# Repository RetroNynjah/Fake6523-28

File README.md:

# Fake6523-28
This is a replacement for the 28-pin version of the MOS 6523 tri-port interface used in the Commodore 1551 paddle.

This replacement is pretty much a scaled down version of the 40-pin [Fake6523](https://github.com/go4retro/Fake6523) created by Jim Brain. 
The verilog code for the CPLD is based on code created by Maciej Witkowiak for the [TCBM2SD](https://github.com/ytmytm/plus4-tcbm2sd).  

## About the 6523

There is no datasheet available for the 28-pin version of the 6523. I'm guessing it was a modification that was made exclusively for the 1551 to fit in the paddle. They seem to be branded either 6523T or 6523A. 
It is quite similar to the 40-pin version but instead of three 8-bit ports it only has one 8-bit port (A) and two 2-bit ports (B and C). Some [old instructions](ref/1551-tia.gif) were available that let you replace a 28-pin 6523 with a 40-pin 6523 or 6525 using an adapter. I based my PCB design on those instructions.

I've tested a real 6523T to find out how it behaves in various conditions and this is what I found. Some of it is obvious and some of it is my best guesses.  
The two 2-bit ports and their corresponding DDR registers are all 8-bit registers internally. The other six bits in a 2-bit port (let's call them extra bits) are all there. They are just not connected to any external pins.
Eight bits can be written to them and wile the bits are configured as outputs (1) in the DDR registers, the same eight bits can be read back from the port register.  
When the extra bits are switched to inputs (0) in the DDR register, they start to float. At first, they retain the data that was last written to the port register but after a second or so, the extra bits start to toggle. The behaviour may seem conistent but it only is until it isn't :)

## Design history

### Rev 1

Revision 1 is based on the obsolete, yet still available CPLD XC9572XL-10VQ64 (VQFP-64).  
I chose to replicate the output funtionality with eight bits in all ports in this version of the HDL. The extra bits are normally not used by the 1551 and the drive works fine without that functionality but if some third party software like a highly optimized loader would use the extra bits for anything, it feels good to have them there for compatibility.

The firmware for Rev 1 is available in the [rev1/hdl](rev1/hdl) folder. There are compiled files in jed and svf formats and the source code is available as a Xilinx ISE project.

### Rev 2
This was a development revision that wasn't released.

### Rev 3
Revision 3 was based on the still active CPLD ATF1504AS (TQFP-44) and PORTB and PORTC was limited internally to two bits each due to space constraints and the unconnected extra bits in PORTB and PORTC always returned 0's. This normally doesn't affect the functionality of the drive and would only be a problem if someone would use these unconnected registers for something. I'm not aware of any software that does that.  
The ATF1504AS is a 5V part. No voltage regulator is necessary and the Atmel CPLD is cheaper than the Xilinx CPLD so the design is simpler and cheaper than the Xilinx design.  
The firmware for Rev 3 is available in the [rev3/hdl](rev3/hdl) folder. There are compiled files in jed and svf formats and the source code is available as a ProChip designer project.  
The rev 3 firmware is only compatible with rev 3 boards.

### Rev 4

Revision 4 is based on the same ATF1504AS CPLD as rev 3. The difference compared to rev 3 is that it once again enables all eight bits in all three port registers. This required a new PCB layout.  
The firmware for Rev 4 is available in the [rev4/hdl](rev4/hdl) folder. There are compiled files in jed and svf formats and the source code is available as a ProChip designer project.  
The rev 4 firmware is only compatible with rev 4 boards.

## Compatibility
The Fake6523-28 has not gone through any long term testing so **use at your own risk**.  
It has briefly been tested as a 1551 paddle TPI together with:
* 1551 CPU
    * MOS 6510T
    * Monotech 6502
* 1551 TPI
    * MOS 6525A
    * Fake6523
* Plus/4 CPUs and CPU replacements
    * MOS 8501R1
    * Zaxon FGPA
    * 6510 adapter
    * dmantione (6502)
    * Monotech (6502)
    * Firecpu7501 (6502)
* Plus/4 Kernal
    * CBM original
    * 6510 Kernal hack
    * JiffyDOS
* Plus/4 PLA
    * MOS 251641-02
    * PLA16V8
    * Retroninja CPLD PLA
* Paddle PLA
    * Original 251641-03
    * FlashPLA 55/70ns
    * Retroninja CPLD PLA
    * Retroninja 16V8 PLA

Rev 3 has been tested even less but should hopefully work the same.

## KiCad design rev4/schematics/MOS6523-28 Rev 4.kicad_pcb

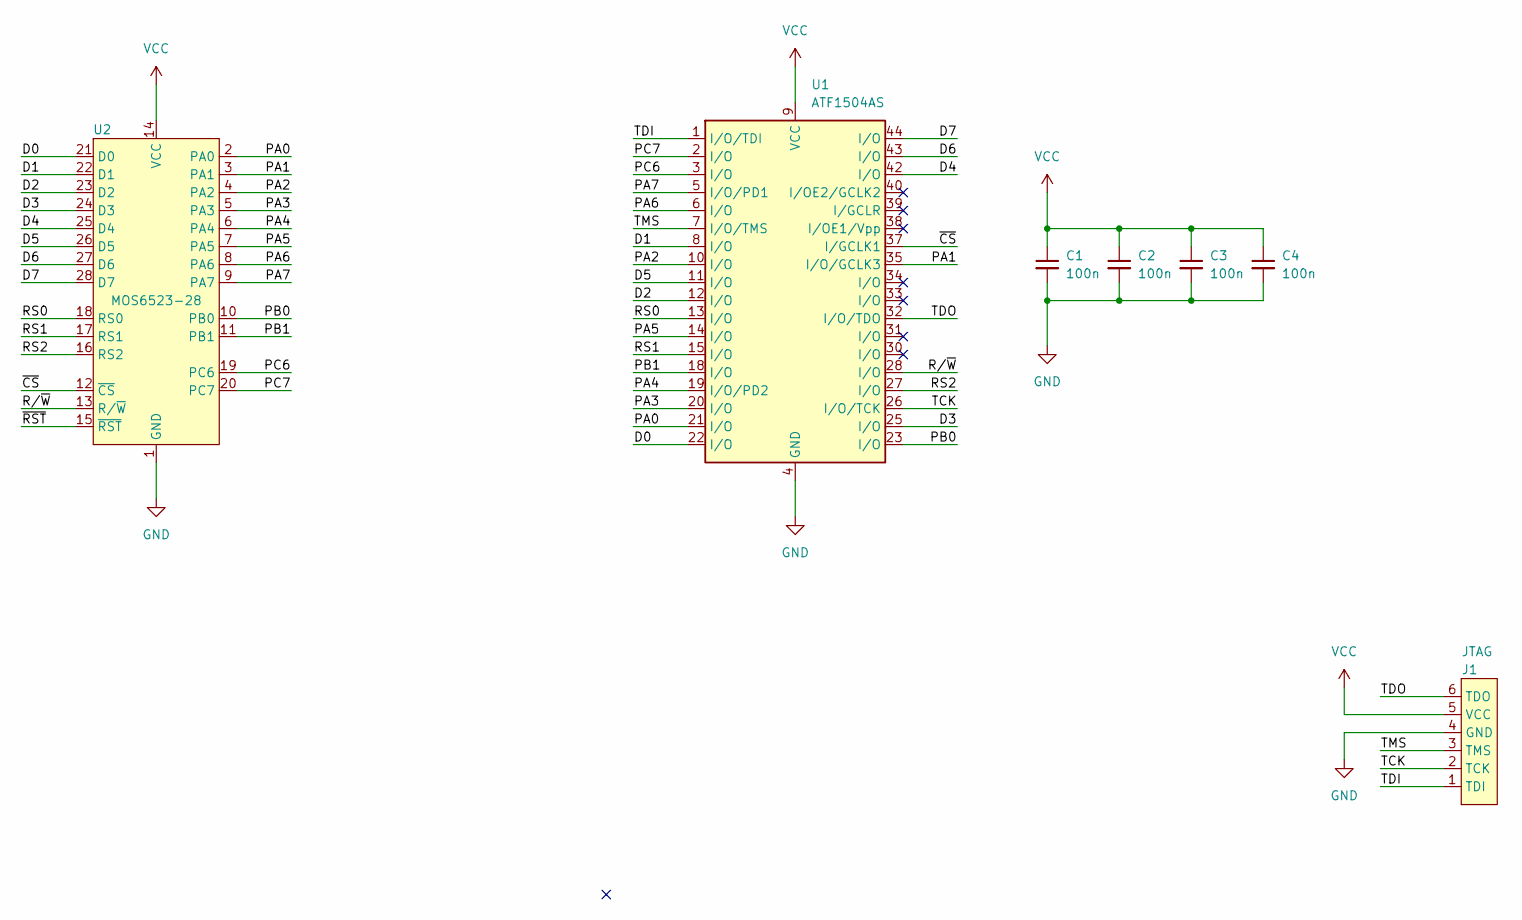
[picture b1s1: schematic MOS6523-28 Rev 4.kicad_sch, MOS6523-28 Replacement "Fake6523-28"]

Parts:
C1, C2, C3, C4: 100n; C_0603_1608Metric_Pad1.08x0.95mm_HandSolder
J1: JTAG; PinHeader_2x03_P2.54mm_Vertical
U1: ATF1504AS; TQFP-44_10x10mm_P0.8mm
U2: MOS6523-28; DIP-28_W15.24mm_BottomHeadersFlat

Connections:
/D0: U1.22 (I/O), U2.21 (D0)
/D1: U1.8 (I/O), U2.22 (D1)
/D2: U1.12 (I/O), U2.23 (D2)
/D3: U1.25 (I/O), U2.24 (D3)
/D4: U1.42 (I/O), U2.25 (D4)
/D5: U1.11 (I/O), U2.26 (D5)
/D6: U1.43 (I/O), U2.27 (D6)
/D7: U1.44 (I/O), U2.28 (D7)
/PA0: U1.21 (I/O), U2.2 (PA0)
/PA1: U1.35 (I/O/GCLK3), U2.3 (PA1)
/PA2: U1.10 (I/O), U2.4 (PA2)
/PA3: U1.20 (I/O), U2.5 (PA3)
/PA4: U1.19 (I/O/PD2), U2.6 (PA4)
/PA5: U1.14 (I/O), U2.7 (PA5)
/PA6: U1.6 (I/O), U2.8 (PA6)
/PA7: U1.5 (I/O/PD1), U2.9 (PA7)
/PB0: U1.23 (I/O), U2.10 (PB0)
/PB1: U1.18 (I/O), U2.11 (PB1)
/PC6: U1.3 (I/O), U2.19 (PC6)
/PC7: U1.2 (I/O), U2.20 (PC7)
/RS0: U1.13 (I/O), U2.18 (RS0)
/RS1: U1.15 (I/O), U2.17 (RS1)
/RS2: U1.27 (I/O), U2.16 (RS2)
/R/~W: U1.28 (I/O), U2.13 (R/~W)
/TCK: J1.2 (TCK), U1.26 (I/O/TCK)
/TDI: J1.1 (TDI), U1.1 (I/O/TDI)
/TDO: J1.6 (TDO), U1.32 (I/O/TDO)
/TMS: J1.3 (TMS), U1.7 (I/O/TMS)
/~CS: U1.37 (I/GCLK1), U2.12 (~CS)
/~RST: U2.15 (~RST)
GND: C1.2, C2.2, C3.2, C4.2, J1.4 (GND), U1.4 (GND), U1.16 (GND), U1.24 (GND), U1.36 (GND), U2.1 (GND)
VCC: C1.1, C2.1, C3.1, C4.1, J1.5 (VCC), U1.9 (VCC), U1.17 (VCC), U1.29 (VCC), U1.41 (VCC), U2.14 (VCC)

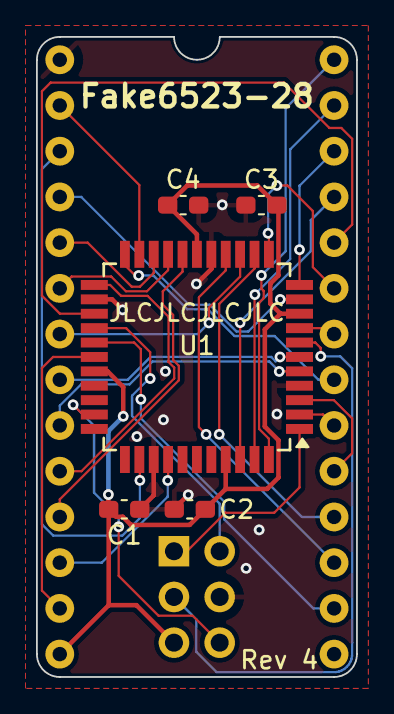
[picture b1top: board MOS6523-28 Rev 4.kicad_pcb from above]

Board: 2 copper layers, 17.8 x 35.6 mm, 7 parts (0 on the bottom side), 31 nets.

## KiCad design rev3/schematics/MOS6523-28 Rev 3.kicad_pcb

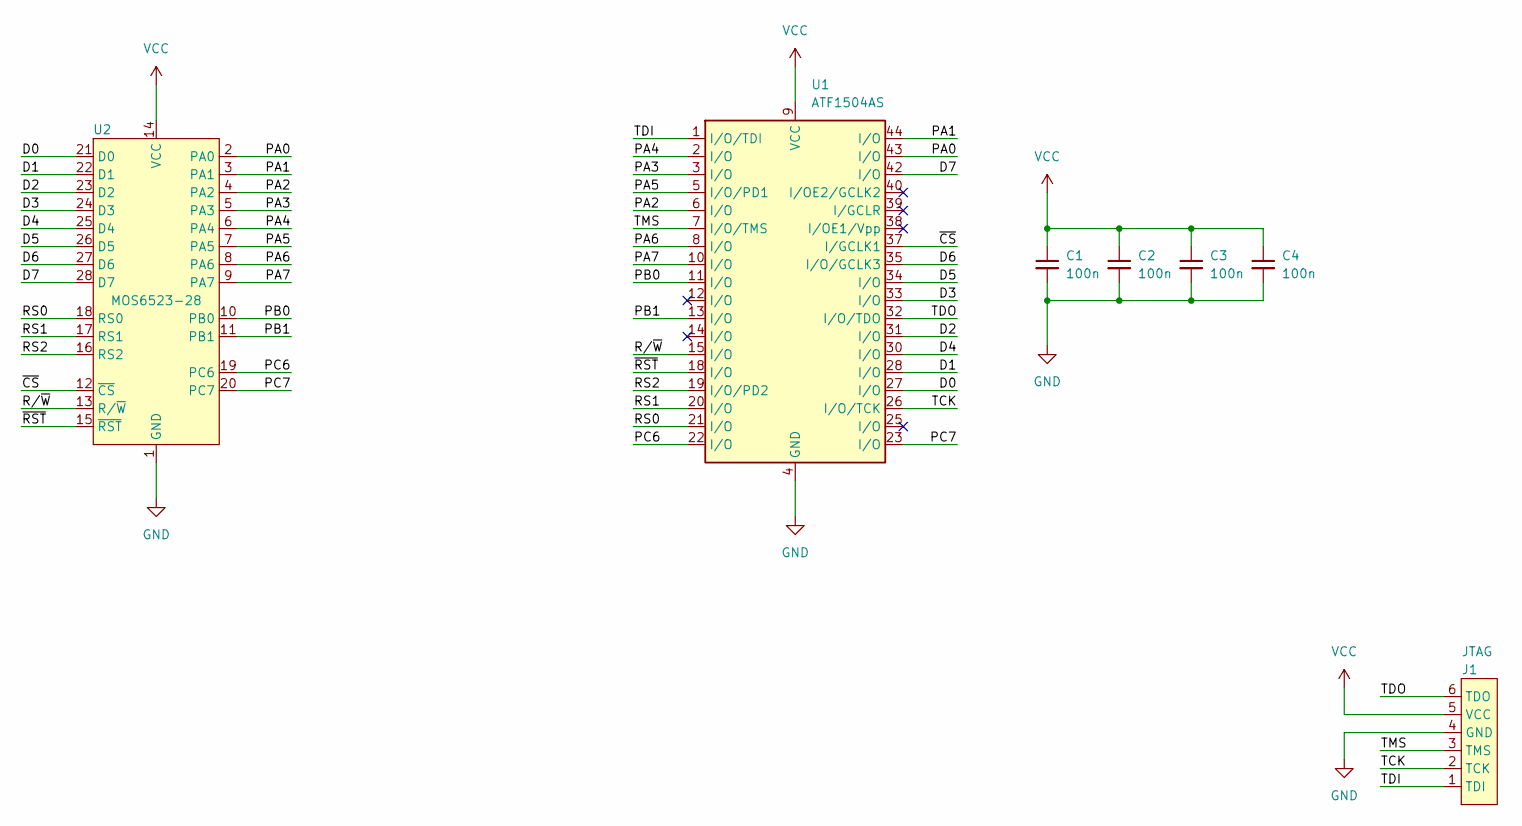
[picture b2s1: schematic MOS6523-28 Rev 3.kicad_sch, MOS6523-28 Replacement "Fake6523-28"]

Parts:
C1, C2, C3, C4: 100n; C_0603_1608Metric_Pad1.08x0.95mm_HandSolder
J1: JTAG; PinHeader_2x03_P2.54mm_Vertical
U1: ATF1504AS; TQFP-44_10x10mm_P0.8mm
U2: MOS6523-28; DIP-28_W15.24mm_BottomHeadersFlat

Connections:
/D0: U1.27 (I/O), U2.21 (D0)
/D1: U1.28 (I/O), U2.22 (D1)
/D2: U1.31 (I/O), U2.23 (D2)
/D3: U1.33 (I/O), U2.24 (D3)
/D4: U1.30 (I/O), U2.25 (D4)
/D5: U1.34 (I/O), U2.26 (D5)
/D6: U1.35 (I/O/GCLK3), U2.27 (D6)
/D7: U1.42 (I/O), U2.28 (D7)
/PA0: U1.43 (I/O), U2.2 (PA0)
/PA1: U1.44 (I/O), U2.3 (PA1)
/PA2: U1.6 (I/O), U2.4 (PA2)
/PA3: U1.3 (I/O), U2.5 (PA3)
/PA4: U1.2 (I/O), U2.6 (PA4)
/PA5: U1.5 (I/O/PD1), U2.7 (PA5)
/PA6: U1.8 (I/O), U2.8 (PA6)
/PA7: U1.10 (I/O), U2.9 (PA7)
/PB0: U1.11 (I/O), U2.10 (PB0)
/PB1: U1.13 (I/O), U2.11 (PB1)
/PC6: U1.22 (I/O), U2.19 (PC6)
/PC7: U1.23 (I/O), U2.20 (PC7)
/RS0: U1.21 (I/O), U2.18 (RS0)
/RS1: U1.20 (I/O), U2.17 (RS1)
/RS2: U1.19 (I/O/PD2), U2.16 (RS2)
/R/~W: U1.15 (I/O), U2.13 (R/~W)
/TCK: J1.2 (TCK), U1.26 (I/O/TCK)
/TDI: J1.1 (TDI), U1.1 (I/O/TDI)
/TDO: J1.6 (TDO), U1.32 (I/O/TDO)
/TMS: J1.3 (TMS), U1.7 (I/O/TMS)
/~CS: U1.37 (I/GCLK1), U2.12 (~CS)
/~RST: U1.18 (I/O), U2.15 (~RST)
GND: C1.2, C2.2, C3.2, C4.2, J1.4 (GND), U1.4 (GND), U1.16 (GND), U1.24 (GND), U1.36 (GND), U2.1 (GND)
VCC: C1.1, C2.1, C3.1, C4.1, J1.5 (VCC), U1.9 (VCC), U1.17 (VCC), U1.29 (VCC), U1.41 (VCC), U2.14 (VCC)

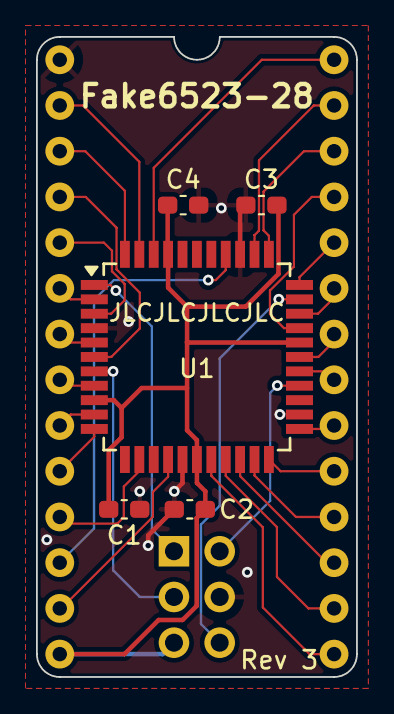
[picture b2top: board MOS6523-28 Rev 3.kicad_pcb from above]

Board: 2 copper layers, 17.8 x 35.6 mm, 7 parts (0 on the bottom side), 32 nets.

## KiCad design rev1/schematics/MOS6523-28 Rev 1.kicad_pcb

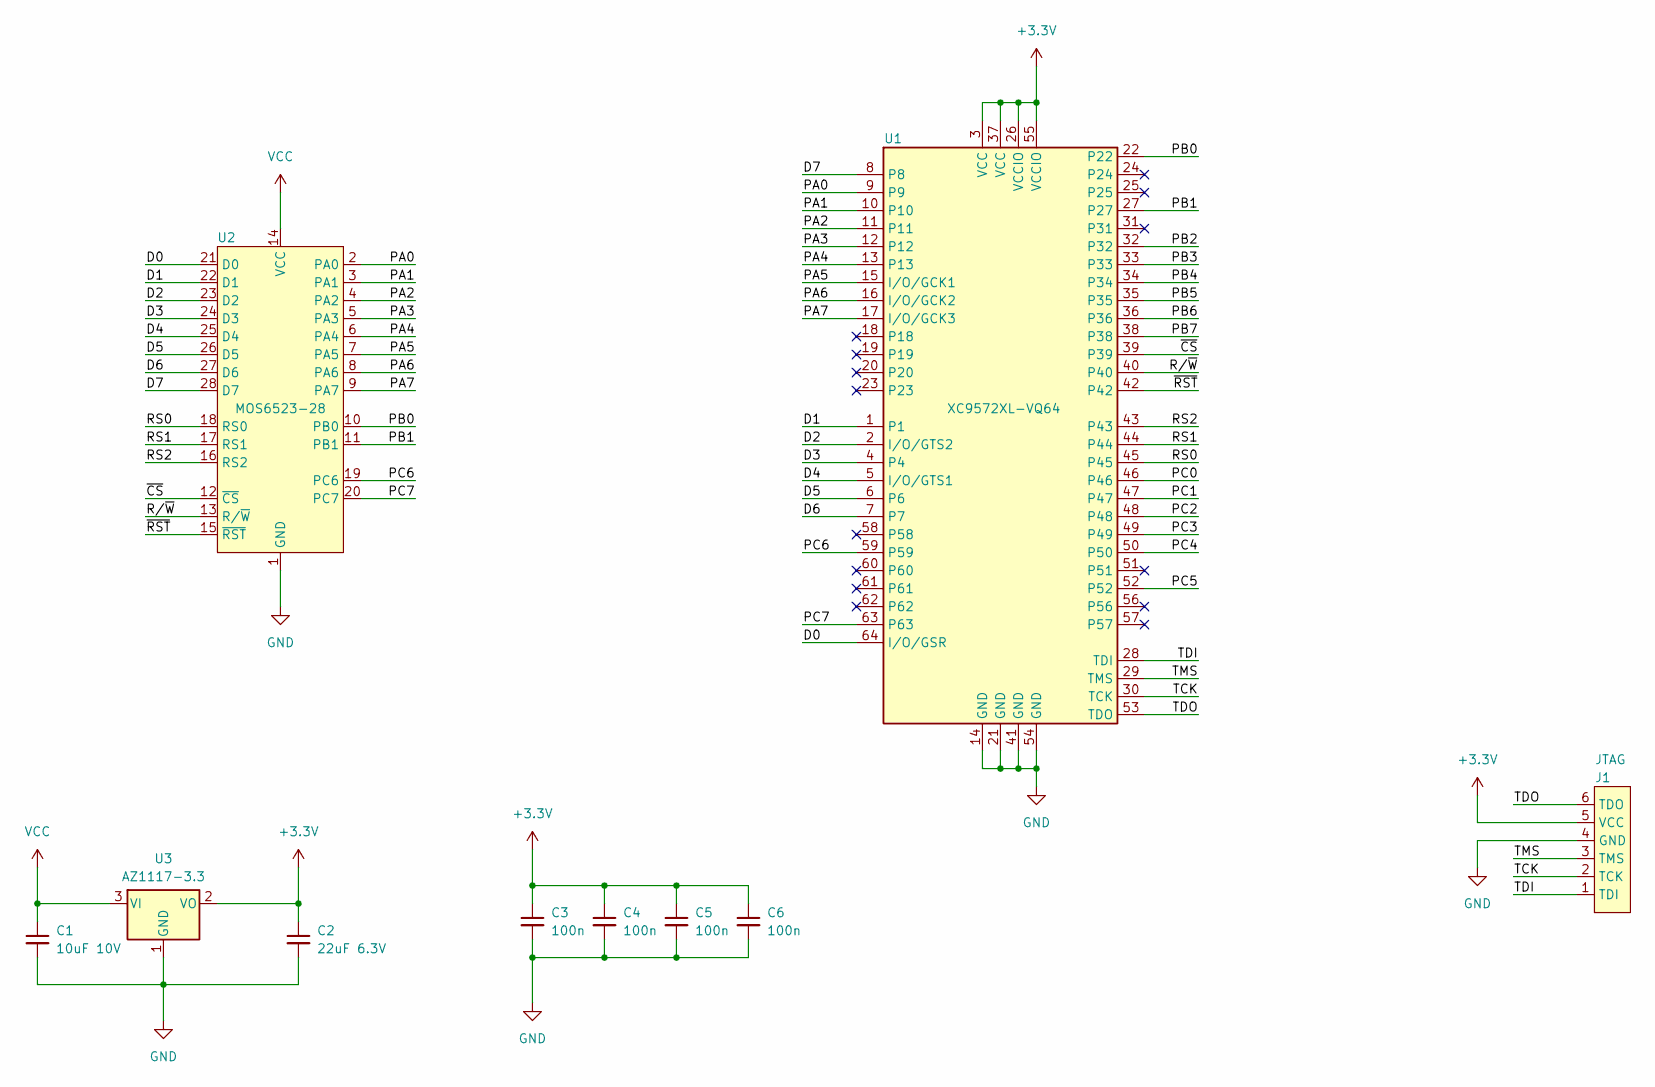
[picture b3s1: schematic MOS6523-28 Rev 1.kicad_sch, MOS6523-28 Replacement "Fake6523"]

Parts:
C1: 10uF 10V; C_0603_1608Metric_Pad1.08x0.95mm_HandSolder
C2: 22uF 6.3V; C_0603_1608Metric_Pad1.08x0.95mm_HandSolder
C3, C4, C5, C6: 100n; C_0603_1608Metric_Pad1.08x0.95mm_HandSolder
J1: JTAG; PinHeader_2x03_P2.54mm_Vertical
U1: XC9572XL-VQ64; TQFP-64_10x10mm_P0.5mm
U2: MOS6523-28; DIP-28_W15.24mm_BottomHeadersFlat
U3: AZ1117-3.3; SOT-89-3_Handsoldering

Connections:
+3.3V: C2.1, C3.1, C4.1, C5.1, C6.1, J1.5 (VCC), U1.3 (VCC), U1.26 (VCCIO), U1.37 (VCC), U1.55 (VCCIO), U3.2 (VO)
/D0: U1.64 (I/O/GSR), U2.21 (D0)
/D1: U1.1, U2.22 (D1)
/D2: U1.2 (I/O/GTS2), U2.23 (D2)
/D3: U1.4, U2.24 (D3)
/D4: U1.5 (I/O/GTS1), U2.25 (D4)
/D5: U1.6, U2.26 (D5)
/D6: U1.7, U2.27 (D6)
/D7: U1.8, U2.28 (D7)
/PA0: U1.9, U2.2 (PA0)
/PA1: U1.10, U2.3 (PA1)
/PA2: U1.11, U2.4 (PA2)
/PA3: U1.12, U2.5 (PA3)
/PA4: U1.13, U2.6 (PA4)
/PA5: U1.15 (I/O/GCK1), U2.7 (PA5)
/PA6: U1.16 (I/O/GCK2), U2.8 (PA6)
/PA7: U1.17 (I/O/GCK3), U2.9 (PA7)
/PB0: U1.22, U2.10 (PB0)
/PB1: U1.27, U2.11 (PB1)
/PB2: U1.32
/PB3: U1.33
/PB4: U1.34
/PB5: U1.35
/PB6: U1.36
/PB7: U1.38
/PC0: U1.46
/PC1: U1.47
/PC2: U1.48
/PC3: U1.49
/PC4: U1.50
/PC5: U1.52
/PC6: U1.59, U2.19 (PC6)
/PC7: U1.63, U2.20 (PC7)
/RS0: U1.45, U2.18 (RS0)
/RS1: U1.44, U2.17 (RS1)
/RS2: U1.43, U2.16 (RS2)
/R/~W: U1.40, U2.13 (R/~W)
/TCK: J1.2 (TCK), U1.30 (TCK)
/TDI: J1.1 (TDI), U1.28 (TDI)
/TDO: J1.6 (TDO), U1.53 (TDO)
/TMS: J1.3 (TMS), U1.29 (TMS)
/~CS: U1.39, U2.12 (~CS)
/~RST: U1.42, U2.15 (~RST)
GND: C1.2, C2.2, C3.2, C4.2, C5.2, C6.2, J1.4 (GND), U1.14 (GND), U1.21 (GND), U1.41 (GND), U1.54 (GND), U2.1 (GND), U3.1 (GND)
VCC: C1.1, U2.14 (VCC), U3.3 (VI)

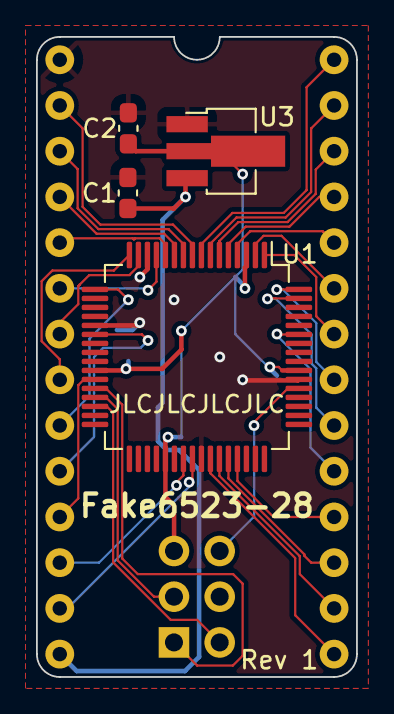
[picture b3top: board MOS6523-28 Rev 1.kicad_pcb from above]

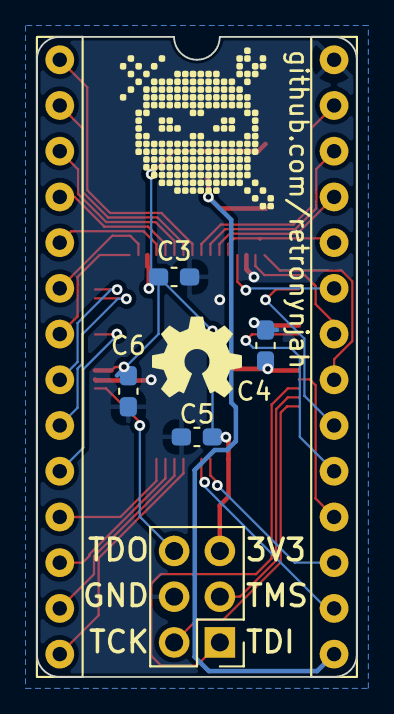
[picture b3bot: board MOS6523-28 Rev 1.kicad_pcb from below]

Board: 2 copper layers, 17.8 x 35.6 mm, 10 parts (5 on the bottom side), 33 nets.

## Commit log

2024-10-27 First upload
2024-10-31 Updated readme with pinout adn tested configurations
2024-11-03 HDL and README updated
    New HDL version with 8-bit registers for PRA & PRB. They read the internal databits if they are set as outputs.
    README updated after research
2025-01-27 Rev 3 released
    Released PCB rev 3 based on ATF1504
2025-01-27 Images corrected
2025-02-23 Update README.md
    Rev 4
2025-03-22 Rev 4 PCB and firmware
2025-03-22 Update README.md
    Revision 4
